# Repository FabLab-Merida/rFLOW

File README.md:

# rFLOW - FabLab Mérida

Proyecto made in FabLab Mérida por el cual mediante el reciclaje de una antigua plancha de vapor y algunos componentes electronicos, se ha convertido en una estación de soldadura BGA monocapa. Capaz de llegar hasta 250º, ideal para multiples tipos de pasta de estaño.

## Motivación  

La principal motivación tras este proyecto es buscar una solución económica a la creacion de PCBs y reparación de estas promoviendo la economia circular y el reciclaje de componentes y piezas.

## Materiales 

1 * Relé de 5V que soporte como miínimo 250V y 13A. <br />
1 * Termistor (vease el .ino para mas información). <br />
1 * Resistencia de la plancha de vapor. <br />
1 * Baquelita monocapa virgen. <br />
1 * ATMEGA 328p. <br />
3 * Botones Push. <br />
3 * Resistencias de 1kO. <br />
1 * Resistencia de 4.7kO. <br />
1 * Condensador de 10uF. <br />
1 * Potenciometro 10kO. <br />
1 * LCD 16*4 segmentos. <br />

## Resultados

La posibilidad de usar un amplio rango de temperatura estable ha dado lugar a múltiples aplicaciones extra, desde el anteriormente mencionada creación de PCBs pasando por facilitar soldaduras por aire manteniendo la zona caliente o secado de filamento de impresora 3D.

## Observaciones

Se necesita que el Atmega use la frecuencia de relog interna de 8MHz, para ello se necesita grabar el bootloader por uno sin los parametros de Arduino, en la bibliografía encontrará información de como hacerlo.

## Bibliografía

LiquidCrystal.h          ==> https://www.arduino.cc/reference/en/libraries/liquidcrystal/ <br />
thermistor.h             ==> https://github.com/miguel5612/ThermistorLibrary <br />
Grabar bootloader        ==> https://docs.arduino.cc/built-in-examples/arduino-isp/ArduinoToBreadboard <br />

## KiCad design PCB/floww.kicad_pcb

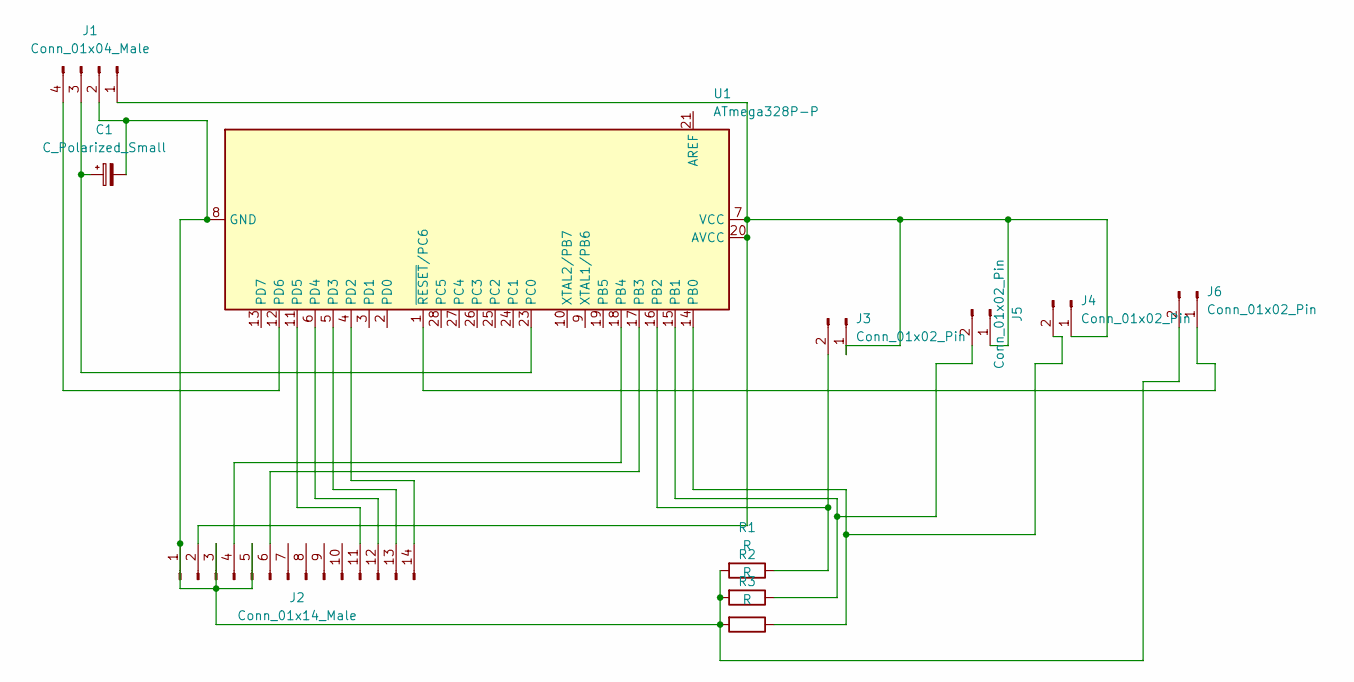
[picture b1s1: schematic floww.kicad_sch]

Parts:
C1: C_Polarized_Small; CP_Radial_D5.0mm_P2.50mm
J1: Conn_01x04_Male; PinHeader_1x04_P2.54mm_Vertical
J2: Conn_01x14_Male; PinHeader_1x14_P2.54mm_Vertical
J3, J4, J5, J6: Conn_01x02_Pin; PinHeader_1x02_P2.54mm_Vertical
R1, R2, R3: R; R_Axial_DIN0207_L6.3mm_D2.5mm_P10.16mm_Horizontal
U1: ATmega328P-P; DIP-28_W7.62mm

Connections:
unnamed: J1.1, J2.2, J3.1, J4.1, J5.1, U1.7 (VCC), U1.20 (AVCC)
unnamed: C1.2, J1.2, J2.1, J2.3, J2.5, J6.2, R1.2, R2.2, R3.2, U1.8 (GND), U1.22 (GND)
unnamed: C1.1, J1.3, U1.23 (PC0)
unnamed: J1.4, U1.12 (PD6)
unnamed: J2.4, U1.18 (PB4)
unnamed: J2.6, U1.17 (PB3)
unnamed: J2.11, U1.11 (PD5)
unnamed: J2.12, U1.6 (PD4)
unnamed: J2.13, U1.5 (PD3)
unnamed: J2.14, U1.4 (PD2)
unnamed: J3.2, R1.1, U1.16 (PB2)
unnamed: J4.2, R3.1, U1.14 (PB0)
unnamed: J5.2, R2.1, U1.15 (PB1)
unnamed: J6.1, U1.1 (~RESET/PC6)

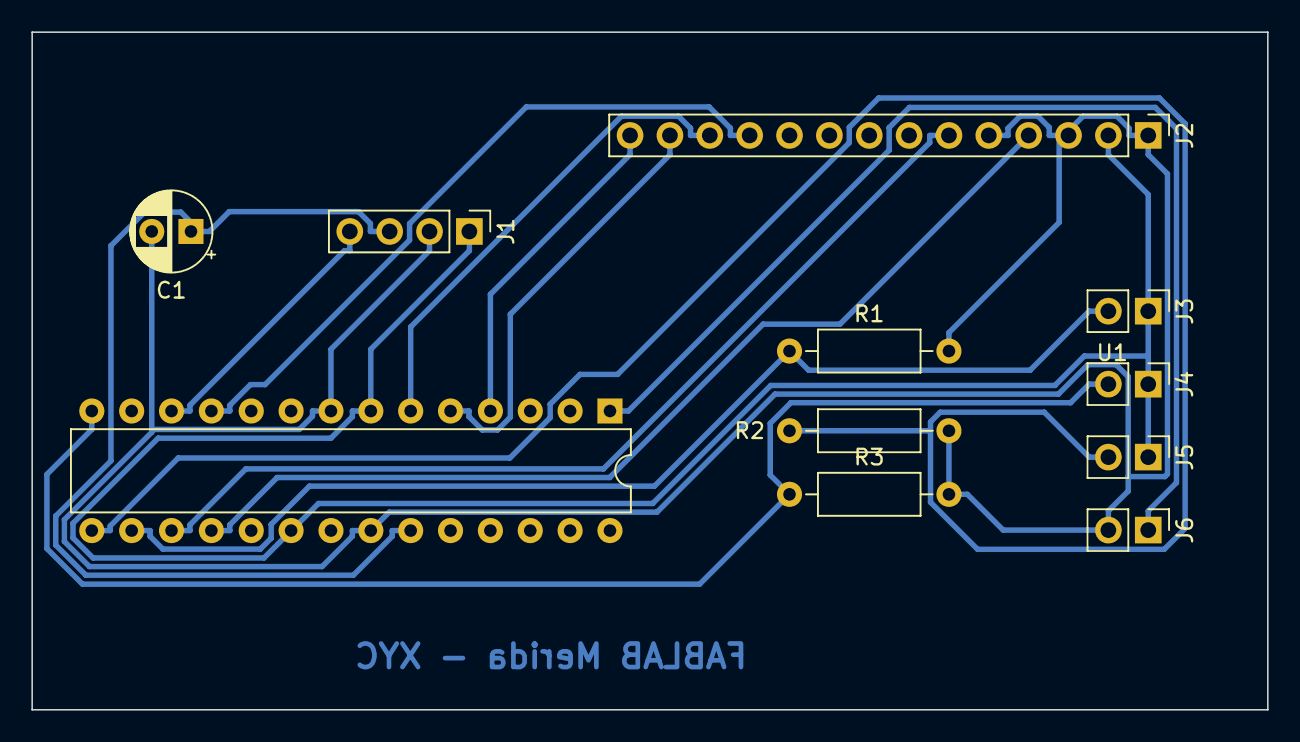
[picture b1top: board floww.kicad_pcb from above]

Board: 2 copper layers, 78.7 x 43.2 mm, 11 parts (0 on the bottom side), 14 nets.

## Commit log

2022-11-18 Add files via upload
    Añadido el esquema del cableado
2022-11-18 Add files via upload
    0.9 RC1
2022-11-28 Create dummy
2022-12-02 Update max/min temp
2022-12-12 Create s
2022-12-12 Create smb
2022-12-13 Versión final y detallitos
2022-12-14 Update rflow.ino
    PARCHE DEL DIA -1
2023-02-01 Update README.md
    RC
2023-02-01 Update README.md
    Casi final
2023-06-13 Create lkjgfvujfdr
